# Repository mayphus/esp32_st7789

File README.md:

my esp32-s3 demo with just st7789

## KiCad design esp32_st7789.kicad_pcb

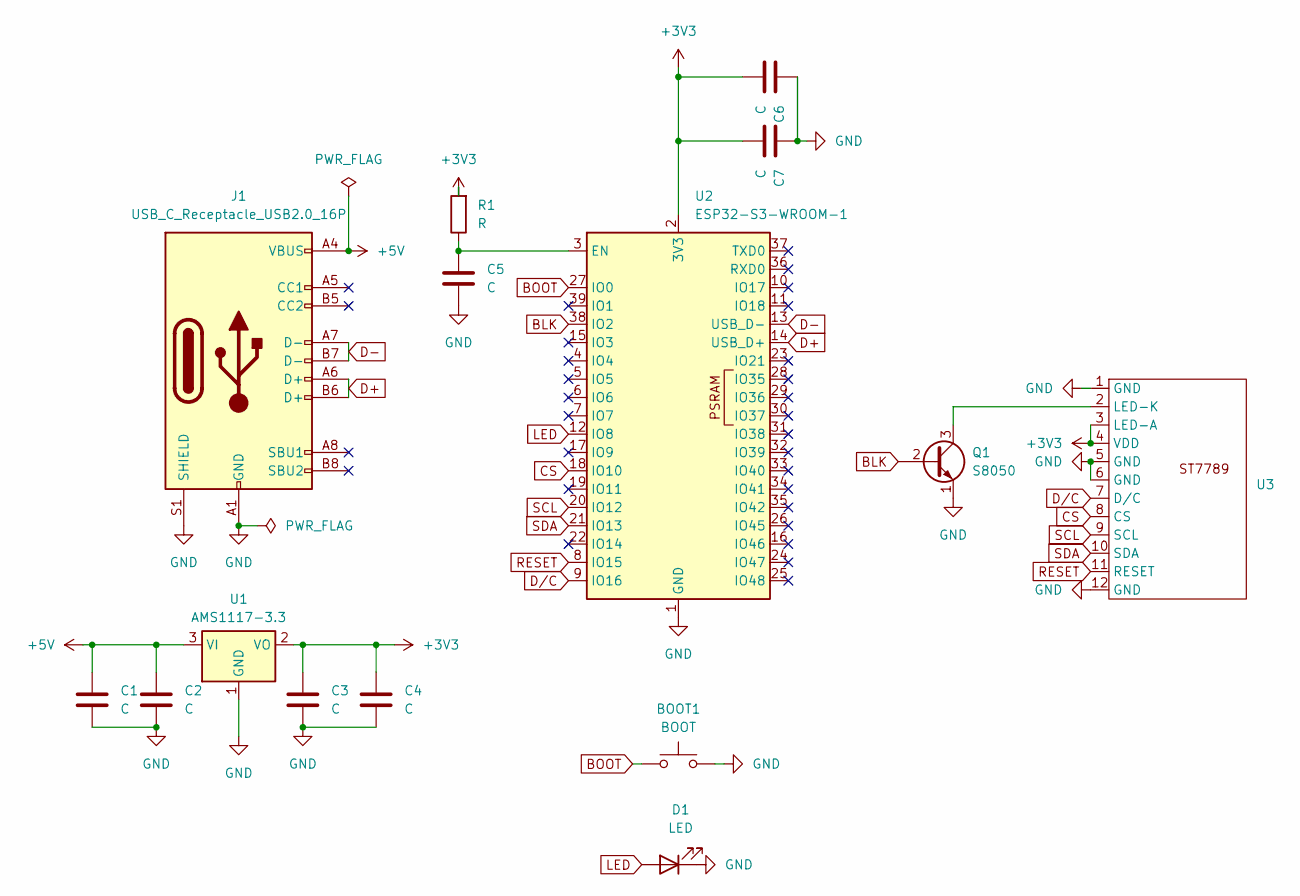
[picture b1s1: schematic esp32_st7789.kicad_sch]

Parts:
BOOT1: BOOT; SW_Push
C1, C2, C3, C4, C5, C6, C7: C; C_0805_2012Metric
D1: LED; LED_0603_1608Metric
J1: USB_C_Receptacle_USB2.0_16P; USB_C_Receptacle_GCT_USB4105-xx-A_16P_TopMnt_Horizontal
Q1: S8050; SOT-23
R1: R; R_0805_2012Metric
U1: AMS1117-3.3; SOT-223-3_TabPin2
U2: ESP32-S3-WROOM-1
U3: ST7789-240x240

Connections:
+3V3: C3.1, C4.1, C6.2, C7.2, R1.2, U1.2 (VO), U2.2 (3V3), U3.3 (LED-A), U3.4 (VDD)
+5V: C1.1, C2.1, J1.A4 (VBUS), J1.A9 (VBUS), J1.B4 (VBUS), J1.B9 (VBUS), U1.3 (VI)
BLK: Q1.2 (B), U2.38 (IO2)
BOOT: BOOT1.1, U2.27 (IO0)
CS: U2.18 (IO10), U3.8 (CS)
D+: J1.A6 (D+), J1.B6 (D+), U2.14 (USB_D+)
D-: J1.A7 (D-), J1.B7 (D-), U2.13 (USB_D-)
D/C: U2.9 (IO16), U3.7 (D/C)
GND: BOOT1.2, C1.2, C2.2, C3.2, C4.2, C5.2, C6.1, C7.1, D1.1 (K), J1.A1 (GND), J1.A12 (GND), J1.B1 (GND), J1.B12 (GND), J1.S1 (SHIELD), Q1.1 (E), U1.1 (GND), U2.1 (GND), U2.40 (GND), U2.41 (GND), U3.1 (GND), U3.5 (GND), U3.6 (GND), U3.12 (GND)
LED: D1.2 (A), U2.12 (IO8)
unnamed: Q1.3 (C), U3.2 (LED-K)
unnamed: C5.1, R1.1, U2.3 (EN)
RESET: U2.8 (IO15), U3.11 (RESET)
SCL: U2.20 (IO12), U3.9 (SCL)
SDA: U2.21 (IO13), U3.10 (SDA)

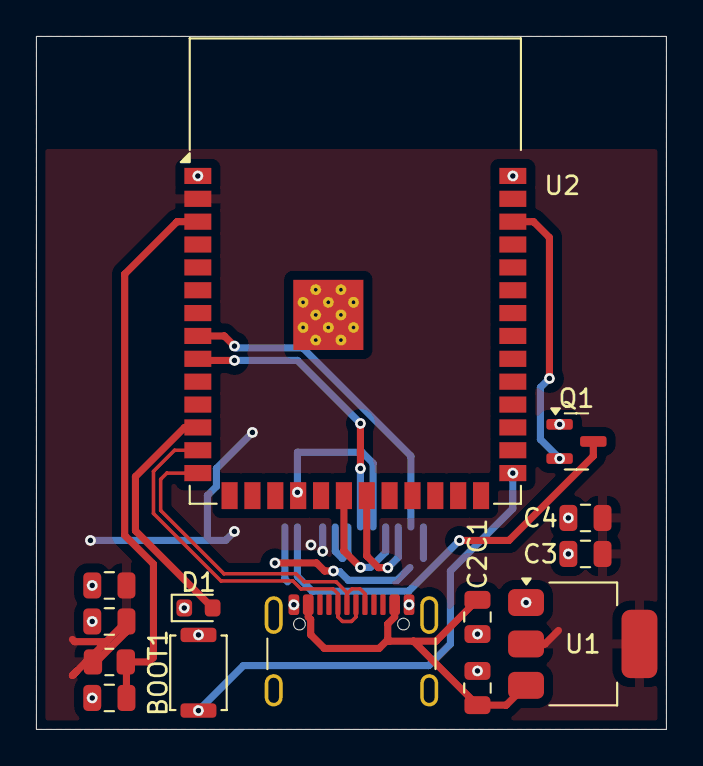
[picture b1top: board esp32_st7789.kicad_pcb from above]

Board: 2 copper layers, 35.0 x 38.5 mm, 15 parts (1 on the bottom side), 15 nets.

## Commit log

2025-02-10 Initialize
2025-02-15 add README.md
